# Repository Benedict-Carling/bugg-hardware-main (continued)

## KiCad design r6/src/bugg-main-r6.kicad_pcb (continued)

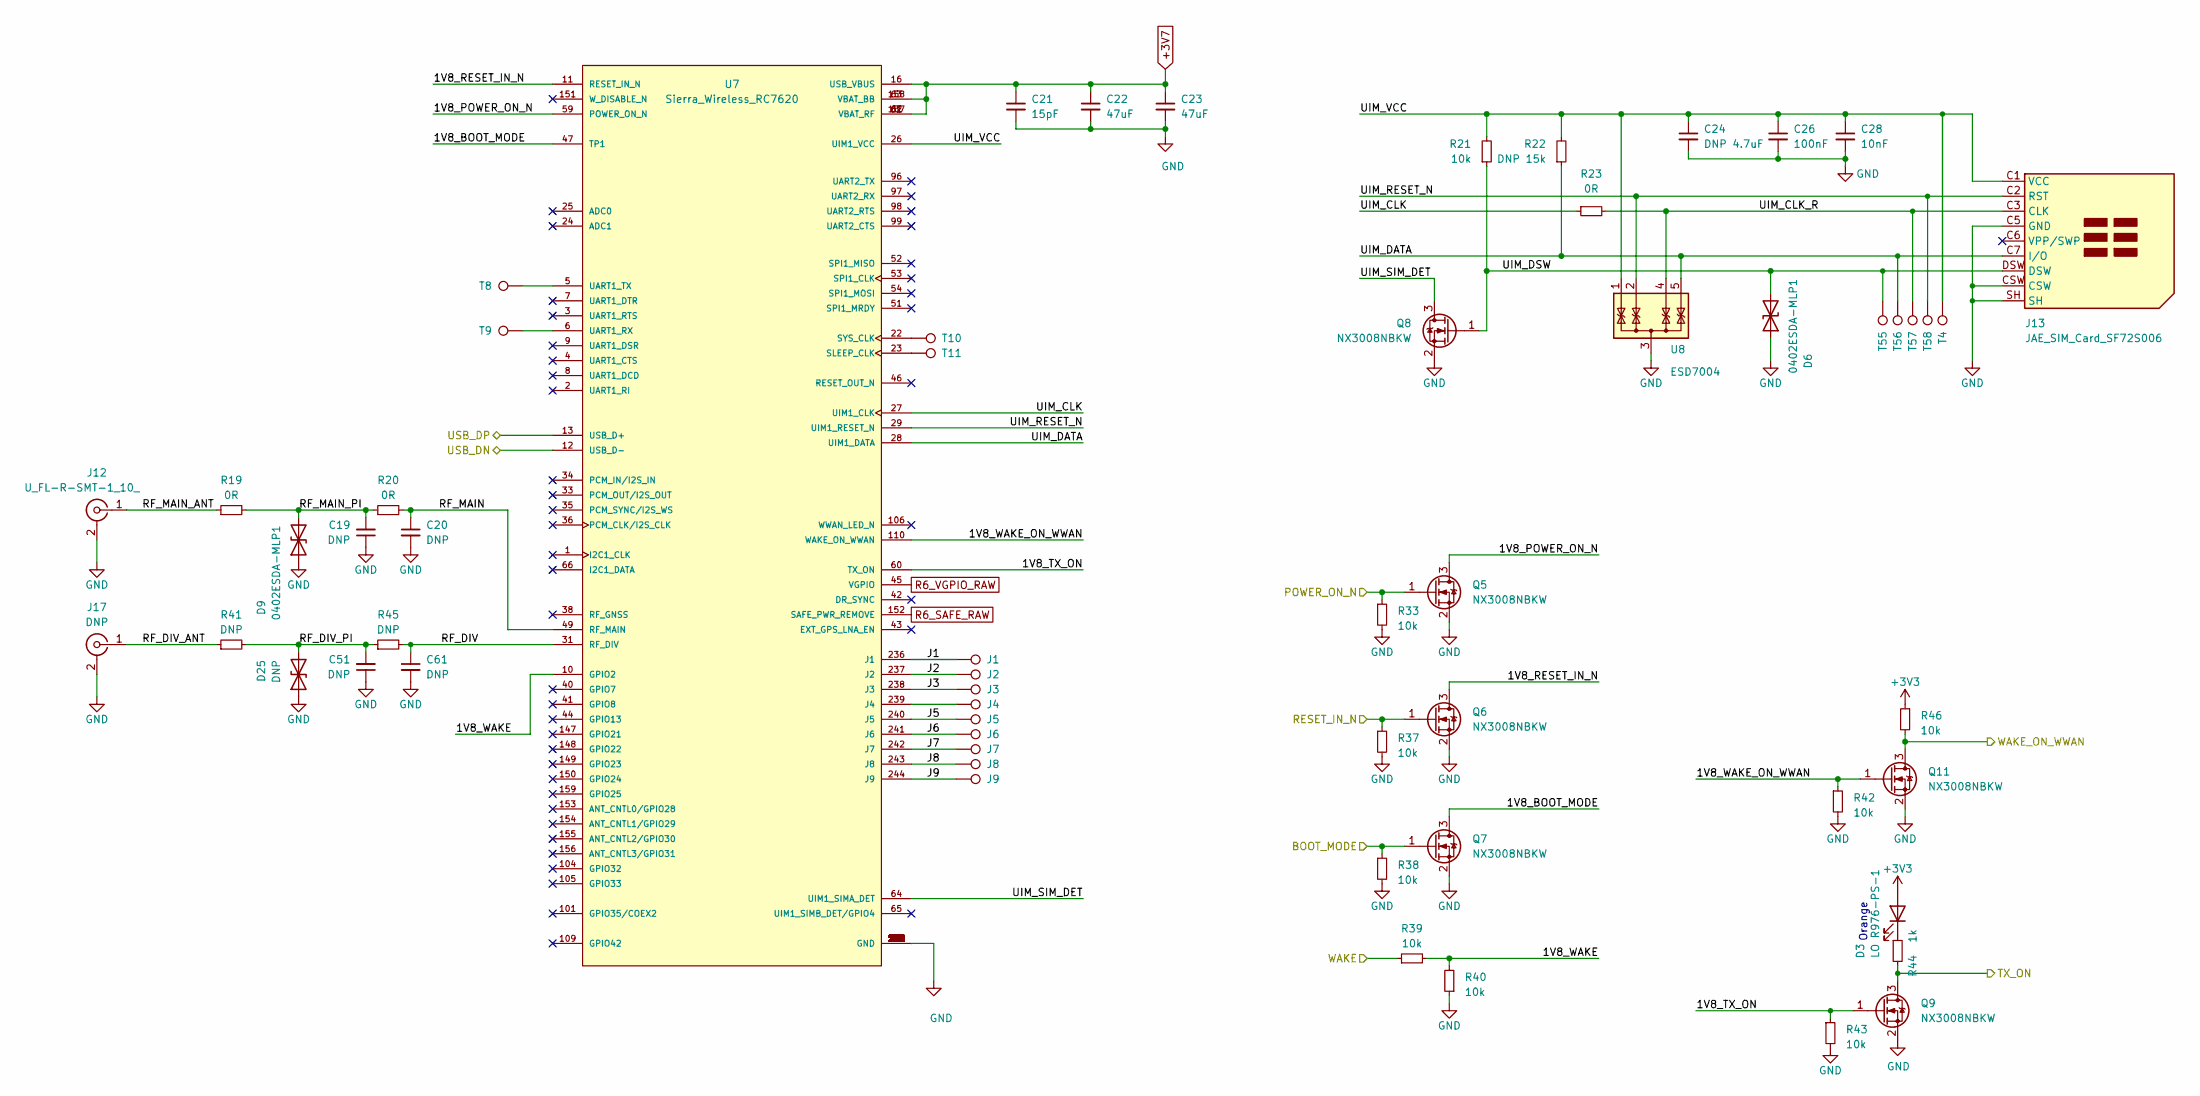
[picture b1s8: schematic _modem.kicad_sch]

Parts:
C19, C20, C51, C61: DNP; C_0402_1005Metric
C21: 15pF; C_0402_1005Metric
C22, C23: 47uF; C_1206_3216Metric; Voltage 6.3V; MPN GRM31CE70J476ME15L; Mouser 81-GRM31CE70J476ME5L
C24: DNP 4.7uF; C_0603_1608Metric
C26: 100nF; C_0402_1005Metric; Voltage 50V; MPN GRM155R71H104KE14D; Mouser 81-GRM155R71H104KE4D
C28: 10nF; C_0402_1005Metric; Voltage 50V
D3: LO R976-PS-1; CHIPLED-0805; MPN LOR976-PS-1; Digikey 475-2488-6-ND
D6, D9: 0402ESDA-MLP1; D_0402_1005Metric; MPN 0402ESDA-MLP1; Digikey 283-2964-6-ND
D25: DNP; D_0402_1005Metric
J1, J2, J3, J4, J5, J6, J7, J8, J9: TestPoint_Pad_D1.0mm
J12: U_FL-R-SMT-1_10_; U.FL_Hirose_U.FL-R-SMT-1-copper-keepout; MPN 128-0711-201; Digikey J983DKR-ND
J13: JAE_SIM_Card_SF72S006; MPN SF72S006VBDR2500; Digikey 670-2967-6-ND
J17: DNP; U.FL_Hirose_U.FL-R-SMT-1-copper-keepout
Q5, Q6, Q7, Q8, Q9, Q11: NX3008NBKW; SOT-323_SC-70; MPN NX3008NBKW; Digikey 1727-1280-6-ND
R19, R20, R23: 0R; R_0402_1005Metric
R21, R33, R37, R38, R39, R40, R42, R43, R46: 10k; R_0402_1005Metric
R22: DNP 15k; R_0402_1005Metric
R41, R45: DNP; R_0402_1005Metric
R44: 1k; R_0402_1005Metric
T4, T8, T9, T10, T11, T55, T56, T57, T58: TestPoint_Pad_D1.0mm
U7: Sierra_Wireless_RC7620; Cellular_Modem-Sierra-Wireless-module-CF3-ringCD; MPN RC7620
U8: ESD7004; USON-10_2.5x1.0mm_P0.5mm; MPN ESD7004MUTAG; Digikey ESD7004MUTAGOSDKR-ND

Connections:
+3V3: D3.2 (A), R46.1; also elsewhere on the board
+3V7: C21.1, C22.1, C23.1, U7.16 (USB_VBUS), U7.61 (VBAT_RF), U7.62 (VBAT_RF), U7.63 (VBAT_BB), U7.157 (VBAT_RF), U7.158 (VBAT_BB); also elsewhere on the board
/BOOT_MODE: Q7.1 (G), R38.1; also elsewhere on the board
/MODEM_USB_DN: U7.12 (USB_D-); also elsewhere on the board
/MODEM_USB_DP: U7.13 (USB_D+); also elsewhere on the board
/Modem/1V8_BOOT_MODE: Q7.3 (D), U7.47 (TP1)
/Modem/1V8_POWER_ON_N: Q5.3 (D), U7.59 (POWER_ON_N)
/Modem/1V8_RESET_IN_N: Q6.3 (D), U7.11 (RESET_IN_N)
/Modem/1V8_TX_ON: Q9.1 (G), R43.1, U7.60 (TX_ON)
/Modem/1V8_WAKE: R39.2, R40.2, U7.10 (GPIO2)
/Modem/1V8_WAKE_ON_WWAN: Q11.1 (G), R42.1, U7.110 (WAKE_ON_WWAN)
/Modem/J1: J1.1, U7.236 (J1)
/Modem/J2: J2.1, U7.237 (J2)
/Modem/J3: J3.1, U7.238 (J3)
/Modem/J5: J5.1, U7.240 (J5)
/Modem/J6: J6.1, U7.241 (J6)
/Modem/J7: J7.1, U7.242 (J7)
/Modem/J8: J8.1, U7.243 (J8)
/Modem/J9: J9.1, U7.244 (J9)
/Modem/RF_DIV: C61.1, R45.2, U7.31 (RF_DIV)
/Modem/RF_DIV_ANT: J17.1 (In), R41.1
/Modem/RF_DIV_PI: C51.2, D25.2 (A2), R41.2, R45.1
/Modem/RF_MAIN: C20.1, R20.2, U7.49 (RF_MAIN)
/Modem/RF_MAIN_ANT: J12.1 (In), R19.1
/Modem/RF_MAIN_PI: C19.2, D9.2 (A2), R19.2, R20.1
/Modem/UIM_CLK: R23.1, U7.27 (UIM1_CLK)
/Modem/UIM_CLK_R: J13.C3 (CLK), R23.2, T57.1, U8.4 (IO3), U8.7
/Modem/UIM_DATA: J13.C7 (I/O), R22.1, T56.1, U7.28 (UIM1_DATA), U8.5 (IO4), U8.6
/Modem/UIM_DSW: D6.2 (A2), J13.DSW, Q8.1 (G), R21.1, T55.1
/Modem/UIM_RESET_N: J13.C2 (RST), T58.1, U7.29 (UIM1_RESET_N), U8.2 (IO2), U8.9
/Modem/UIM_SIM_DET: Q8.3 (D), U7.64 (UIM1_SIMA_DET)
/Modem/UIM_VCC: C24.1, C26.1, C28.1, J13.C1 (VCC), R21.2, R22.2, T4.1, U7.26 (UIM1_VCC), U8.1 (IO1), U8.10
/POWER_ON_N: Q5.1 (G), R33.1; also elsewhere on the board
/RESET_IN_N: Q6.1 (G), R37.1; also elsewhere on the board
/TX_ON: Q9.3 (D), R44.2; also elsewhere on the board
/WAKE: R39.1; also elsewhere on the board
/WAKE_ON_WWAN: Q11.3 (D), R46.2; also elsewhere on the board
GND: C19.1, C20.2, C21.2, C22.2, C23.2, C24.2, C26.2, C28.2, C51.1, C61.2, D6.1 (A1), D9.1 (A1), D25.1 (A1), J12.2 (Ext), J13.C5 (GND), J13.CSW, J13.SH, J17.2 (Ext), Q5.2 (S), Q6.2 (S), Q7.2 (S), Q8.2 (S), Q9.2 (S), Q11.2 (S), R33.2, R37.2, R38.2, R40.1, R42.2, R43.2, U7.30 (GND), U7.32 (GND), U7.37 (GND), U7.39 (GND), U7.48 (GND), U7.50 (GND), U7.67 (GND), U7.68 (GND), U7.69 (GND), U7.70 (GND), U7.111 (GND), U7.113 (GND), U7.125 (GND), U7.128 (GND), U7.136 (GND), U7.139 (GND), U7.167 (GND), U7.168 (GND), U7.169 (GND), U7.170 (GND), U7.171 (GND), U7.172 (GND), U7.173 (GND), U7.174 (GND), U7.175 (GND), U7.176 (GND), U7.177 (GND), U7.178 (GND), U7.179 (GND), U7.180 (GND), U7.181 (GND), U7.182 (GND), U7.183 (GND), U7.184 (GND), U7.185 (GND), U7.186 (GND), U7.187 (GND), U7.188 (GND), U7.189 (GND), U7.190 (GND), U7.191 (GND), U7.192 (GND), U7.193 (GND), U7.194 (GND), U7.195 (GND), U7.196 (GND), U7.197 (GND), U7.198 (GND), U7.199 (GND), U7.200 (GND), U7.201 (GND), U7.202 (GND), U7.203 (GND), U7.204 (GND), U7.205 (GND), U7.206 (GND), U7.207 (GND), U7.208 (GND), U7.209 (GND), U7.210 (GND), U7.211 (GND), U7.212 (GND), U7.213 (GND), U7.214 (GND), U7.215 (GND), U7.216 (GND), U7.217 (GND), U7.218 (GND), U7.219 (GND), U7.220 (GND), U7.221 (GND), U7.222 (GND), U7.223 (GND), U7.224 (GND), U7.225 (GND), U7.226 (GND), U7.227 (GND), U7.228 (GND), U7.229 (GND), U7.230 (GND), U7.231 (GND), U7.232 (GND), U7.233 (GND), U7.234 (GND), U8.3 (G), U8.8; also elsewhere on the board
unnamed: D3.1 (K), R44.1
unnamed: J4.1, U7.239 (J4)
unnamed: T11.1, U7.23 (SLEEP_CLK)
unnamed: T10.1, U7.22 (SYS_CLK)
unnamed: T9.1, U7.6 (UART1_RX)
unnamed: T8.1, U7.5 (UART1_TX)
R6_SAFE_RAW: U7.152 (SAFE_PWR_REMOVE); also elsewhere on the board
R6_VGPIO_RAW: U7.45 (VGPIO); also elsewhere on the board

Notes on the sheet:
Orange

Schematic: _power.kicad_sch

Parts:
C1, C3, C4, C41, C42, C93: 220nF; C_0402_1005Metric; Voltage 50V; MPN GRM155R61H224ME01J; Digikey 490-GRM155R61H224ME01JDKR-ND
C2, C5, C6, C43, C44, C45, C80, C88, C89, C90, C91, C133, C134, C135, C136: 4.7uF; C_1206_3216Metric; Voltage 50V; MPN CL31B475KBHNNNE
C7, C8, C97, C98, C99, C100, C111, C120: 1uF; C_0402_1005Metric; Voltage 6.3V; MPN GRM155C81C105KE15D; Mouser 81-GRM155C81C105KE5D
C9, C10, C17, C18, C87, C101, C105, C106, C117, C121, C138, C139, C141: 100nF; C_0402_1005Metric; Voltage 50V; MPN GRM155R71H104KE14D; Mouser 81-GRM155R71H104KE4D
C11: 18pF; C_0402_1005Metric
C12: 15pF; C_0402_1005Metric
C13, C14, C15, C16, C103: 47uF; C_1206_3216Metric; Voltage 6.3V; MPN GRM31CE70J476ME15L; Mouser 81-GRM31CE70J476ME5L
C85, C86, C140: 4.7uF; C_0603_1608Metric; Voltage 6.3V; MPN CL10A475KQ8NNNC
C92, C116: 3.3pF; C_0402_1005Metric
C94, C122, C123, C124, C125, C126: DNP; C_0402_1005Metric
C95: 4.7nF; C_0402_1005Metric
C96, C113, C115: 10nF; C_0402_1005Metric; Voltage 50V
C102, C104: 10uF; C_0603_1608Metric; Voltage 6.3V; MPN CL10A106MQ8NNNC; Mouser 187-CL10A106MQ8NNNC
C107, C108, C109: 10uF; C_1210_3225Metric; Voltage 50V; MPN GCM32EC71H106KA03L; Mouser 81-GCM32EC71H106KA3L
C110, C114: 5.8pF; C_0402_1005Metric
C112: 180pF; C_0402_1005Metric
C118, C119: 22uF; CP_Elec_5x5.8; Voltage 25V; MPN UCL1E220MCL1GS; Digikey 493-3932-1-ND
C127, C128, C129, C130, C131: DNP; C_1206_3216Metric
D4: ATV02W360B-HF; D_SOD-123; MPN ATV02W360B-HF; Digikey 641-1664-6-ND
D5: 12V; D_SOD-123; MPN BZT52C12-13-F; Digikey BZT52C1213-FDIDKR-ND
D16, D17, D18, D19: PMEG6020ETR; Nexperia_CFP3_SOD-123W; MPN PMEG6020ETR,115; Digikey 1727-1347-1-ND
D21, D22: SMF4L48CA; D_SOD-123F; MPN SMF4L48CA; Mouser 576-SMF4L48CA
D23, D24: DNP; D_SOD-123F
FB3, FB4, FB5, FB6: 1k@100MHz; L_0603_1608Metric; MPN BLM18KG102SN1D; Digikey 490-17349-1-ND
J10: 502443-0860; Molex_CLIK-Mate_502443-0870_1x08-2MP_P2.00mm_Vertical; MPN 502443-0860; Digikey Molex
L1: 4.7uH; L_Coilcraft_XAL5030-XXX; MPN XAL5030-472MEC; Mouser 994-XAL5030-472MEC
L2: 3.3uH; L_Coilcraft_XAL5030-XXX; MPN XAL5030-332MEC; Mouser 994-XAL5030-332MEC
L3, L4: 4.7uH; L_Coilcraft_XxL4030; MPN XAL4030-472MEC; Mouser 994-XAL4030-472MEC
L5: 15uH; L_Wuerth_MAPI-4020; MPN 74438356150; Mouser 710-74438356150
L6, L7, L8: 1uH; L_1008_2520Metric; MPN LQM2HPN1R0MJHL; Digikey 490-12068-6-ND
NT1: NetTie_2; NetTie-2_SMD_Pad2.0mm-inner1
Q1, Q2, Q3: Si7113ADN; Vishay_PowerPAK_1212-8_Single; MPN SI7113ADN-T1-GE3; Digikey SI7113ADN-T1-GE3DKR-ND
Q10: Si2323DS; SOT-23; MPN SI2323DS-T1
Q26: 2SD1782KT146R; SC-59; MPN 2SD1782KT146R; Mouser 755-2SD1782KT146R
R6: 10k; R_0402_1005Metric
R7, R8, R11, R12, R13, R14, R16, R88: 100k; R_0402_1005Metric
R9, R10, R90: 1M; R_0402_1005Metric
R15: 22.6k; R_0402_1005Metric
R17: 37.4k; R_0402_1005Metric
R18, R83, R99, R102, R103, R107, R108: 0R; R_0402_1005Metric
R35, R36: 0.1R; R_0402_1005Metric
R78, R101: DNP; R_0402_1005Metric
R87: 100R; R_0402_1005Metric
R89, R98: 510R; R_0402_1005Metric
R91: 976k; R_0402_1005Metric
R92: 85.6k; R_0402_1005Metric
R93: 105k; R_0402_1005Metric
R94: 1.3M; R_0402_1005Metric
R95: 34.8k; R_0402_1005Metric
R96: 180k; R_0402_1005Metric
R97: 45.3k; R_0402_1005Metric
R104: 100R; R_0603_1608Metric; MPN RC0603FR-07100RL
R105, R109, R110: 0R; R_0603_1608Metric
R111, R112: DNP; R_0805_2012Metric
T1, T2, T5, T6, T7, T12, T13, T17, T21, T22, T36, T41, T42, T51, T52: TestPoint_Pad_D1.0mm
U2: ESD7004; USON-10_2.5x1.0mm_P0.5mm; MPN ESD7004MUTAG; Digikey ESD7004MUTAGOSDKR-ND
U3, U4: DZDH0401DW; SOT-363_SC-70-6; MPN DZDH0401DW; Digikey 31-DZDH0401DW-7DKR-ND
U5, U6: LM60440DRPK; WQFN-HR-13; MPN LM60440DRPK; Digikey 595-LM60440DRPKR
U28: TPS65130RGE; VQFN-24-1EP_4x4mm_P0.5mm_EP2.45x2.45mm_ThermalVias; MPN TPS65130RGE; Digikey 296-41861
U29: NCP163ASN330T1G; SOT-23-5; MPN NCP163ASN330T1G; Mouser 863-NCP163ASN330T1G
U30: NCP163ASN180T1G; SOT-23-5; MPN NCP163ASN180T1G; Mouser 863-NCP163ASN180T1G
U31: MAX6105; SOT-23; MPN MAX6105EUR+T; Digikey MAX6105EUR+TCT-ND
U32: LT8362xDD; DFN-10-1EP_3x3mm_P0.5mm_EP1.65x2.38mm; MPN LT8362; Mouser LT8362HDD#PBF
U33: LM7121IM; SOIC-8_3.9x4.9mm_P1.27mm; MPN LM7121IM; Mouser 926-LM7121IMX/NOPB
U35: TPS22810DBV; SOT-23-6; MPN TPS22810DBV; Mouser 595-TPS22810TDBVRQ1

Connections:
+1V8: R105.1; also elsewhere on the board
+3.3VA: R104.1; also elsewhere on the board
+3.3VADC: T2.1, U35.5 (QOD), U35.6 (VOUT); also elsewhere on the board
+3V3: C120.2, U35.1 (VIN); also elsewhere on the board
+3V7: R109.1; also elsewhere on the board
+5V: C86.1, C97.1, C99.1, C101.1, C102.1, C140.1, C141.1, FB3.1, FB4.1, L6.1, Q10.2 (S), R78.1, R87.1, R110.1, U28.5 (INN), U28.6 (INN), U31.1 (IN); also elsewhere on the board
+5VA: T51.1, U31.2 (OUT), U33.3 (+); also elsewhere on the board
+15V: C117.1, R102.1, U33.7 (V+); also elsewhere on the board
+48V: R108.1; also elsewhere on the board
-15V: C121.2, R103.2, U33.4 (V-); also elsewhere on the board
/3V7_EN: R6.1, U6.9 (EN); also elsewhere on the board
/48V_EN: U32.1 (EN/UVLO); also elsewhere on the board
/EXT_MIC_EN: R18.1, R83.1, R88.2, T1.1, U29.3 (EN), U30.3 (EN), U35.3 (EN/UVLO); also elsewhere on the board
/MIC_IN_N: D21.2 (A2), D23.2 (A2), J10.6; also elsewhere on the board
/MIC_IN_P: D22.2 (A2), D24.2 (A2), J10.7; also elsewhere on the board
/P3V3_OUT: R99.2; also elsewhere on the board
/Power and input connector/1V8_O: C100.1, R105.2, T42.1, U30.5 (VOUT)
/Power and input connector/3V7_O: C12.1, C14.1, C16.1, C18.1, L2.2, R13.1, R16.1, R109.2, T12.1
/Power and input connector/5V_O: C11.1, C13.1, C15.1, C17.1, L1.2, Q1.1 (S), Q1.2 (S), Q1.3 (S), R12.1, R14.1, R110.2, T13.1, U3.4 (SOURCE)
/Power and input connector/48V_O: C80.1, C115.1, D19.2 (A), Q26.2 (E), R108.2, T5.1
/Power and input connector/+5V_SW: C85.1, L3.1, Q10.3 (D), R78.2
/Power and input connector/+15V_L: C118.1, FB5.1, R102.2, R111.2, T21.1
/Power and input connector/-15V_L: C119.2, FB6.2, R103.1, R112.1, T22.1
/Power and input connector/BSW: Q10.1 (G), U28.7 (BSW)
/Power and input connector/CN: C95.1, U28.18 (CN)
/Power and input connector/CP: C96.1, U28.21 (CP)
/Power and input connector/FBN: R93.2, R94.1, R101.1, U28.16 (FBN)
/Power and input connector/FBP: C92.2, R91.2, R92.1, U28.22 (FBP)
/Power and input connector/FBX: C110.2, R90.2, R95.1, U32.6 (FBX)
/Power and input connector/INP: D16.2 (A), L3.2, U28.1 (INP), U28.24 (INP)
/Power and input connector/INTVCC: C111.1, U32.3 (INTVCC)
/Power and input connector/LT_VIN: C103.1, C104.2, L5.1, L6.2, T7.1, U32.2 (VIN)
/Power and input connector/LT_VOUT: C105.1, C106.1, C107.1, C108.1, C110.1, D18.1 (K), Q26.3 (C), R89.1, R90.1, T6.1
/Power and input connector/OUTN: D17.1 (K), L4.2, U28.13 (OUTN), U28.14 (OUTN)
/Power and input connector/RT: R97.1, U32.7 (RT)
/Power and input connector/SS: C113.1, U32.8 (SS)
/Power and input connector/SW_3V7: L2.1, U6.12 (SW)
/Power and input connector/SW_5V4: L1.1, U5.12 (SW)
/Power and input connector/SW_48: D18.2 (A), L5.2, U32.10 (SW)
/Power and input connector/TPS_VREF: C93.1, R93.1, U28.17 (VREF)
/Power and input connector/VC: C114.1, R96.1, U32.5 (VC)
/Power and input connector/VIN_DCDC_3V7: C3.1, C5.1, C41.1, L8.2, R36.1, U6.2 (VIN), U6.10 (VIN)
/Power and input connector/VIN_DCDC_5: C4.1, C6.1, C42.1, L7.2, R35.1, U5.2 (VIN), U5.9 (EN), U5.10 (VIN)
/Power and input connector/VIN_F: C87.1, R87.2, U28.4 (VIN)
/Power and input connector/VIN_LDO_1V8: FB4.2, U30.1 (VIN)
/Power and input connector/VIN_LDO_3V3: FB3.2, U29.1 (VIN)
/Power and input connector/VNEG: C90.2, C91.2, C94.2, C134.2, C136.2, C139.2, D17.2 (A), FB6.1, R94.2, U28.15 (VNEG)
/Power and input connector/VPOS: C88.1, C89.1, C92.1, C133.1, C135.1, C138.1, D16.1 (K), FB5.2, R91.1, U28.23 (VPOS)
/Power and input connector/VREF_O: C116.1, R98.2, R107.1, T52.1, U33.6
/Power and input connector/Vin: C1.1, C2.1, C43.1, D5.1 (K), L7.1, L8.1, Q2.1 (S), Q2.2 (S), Q2.3 (S), Q3.1 (S), Q3.2 (S), Q3.3 (S), U4.4 (SOURCE)
/USB_UART_DN: J10.1, U2.1 (IO1), U2.10; also elsewhere on the board
/USB_UART_DP: J10.2, U2.2 (IO2), U2.9; also elsewhere on the board
/VREF: R107.2; also elsewhere on the board
GND: C1.2, C2.2, C3.2, C4.2, C5.2, C6.2, C7.1, C8.1, C13.2, C14.2, C15.2, C16.2, C17.2, C18.2, C41.2, C42.2, C43.2, C44.2, C45.2, C120.1, C122.2, C123.2, C124.2, C125.2, C126.2, C127.2, C128.2, C129.2, C130.2, C131.2, D4.1 (A1), D21.1 (A1), D22.1 (A1), J10.5, NT1.1, R6.2, R7.2, R8.2, R9.2, R10.2, R11.2, R15.2, R17.2, T17.1, T36.1, U2.3 (G), U2.8, U5.1 (PGND), U5.6 (AGND), U5.11 (PGND), U5.13 (PGND), U6.1 (PGND), U6.6 (AGND), U6.11 (PGND), U6.13 (PGND), U35.2 (GND); also elsewhere on the board
GNDA: C80.2, C85.2, C86.2, C87.2, C88.2, C89.2, C90.1, C91.1, C93.2, C95.2, C96.2, C97.2, C98.2, C99.2, C100.2, C101.2, C102.2, C103.2, C104.1, C105.2, C106.2, C107.2, C108.2, C109.2, C111.2, C112.2, C113.2, C114.2, C115.2, C117.2, C118.2, C119.1, C121.1, C122.1, C123.1, C124.1, C125.1, C126.1, C127.1, C128.1, C129.1, C130.1, C131.1, C133.2, C134.1, C135.2, C136.1, C138.2, C139.1, C140.2, C141.2, D23.1 (A1), D24.1 (A1), J10.8, L4.1, NT1.2, R88.1, R92.2, R95.2, R97.2, R111.1, R112.2, U28.2 (PGND), U28.3 (PGND), U28.9 (PSP), U28.11 (PSN), U28.19 (AGND), U28.25 (EP), U29.2 (GND), U30.2 (GND), U31.3 (GND), U32.4 (BIAS), U32.9 (SYNC/MODE), U32.11 (GND); also elsewhere on the board
IN_VIN: D4.2 (A2), J10.3, Q3.5 (D); also elsewhere on the board
unnamed: C44.1, R35.2
unnamed: C45.1, R36.2
unnamed: C94.1, R101.2
unnamed: C112.1, R96.2
unnamed: D5.2 (A), Q3.4 (G), R11.1
unnamed: C109.1, D19.1 (K), Q26.1 (B), R89.2
unnamed: Q1.4 (G), R9.1, U3.3 (BIAS)
unnamed: Q2.4 (G), R10.1, U4.3 (BIAS)
unnamed: R7.1, U3.2 (REF)
unnamed: R8.1, U4.2 (REF)
unnamed: C9.2, U5.4 (BOOT)
unnamed: C11.2, R14.2, R15.1, U5.7 (FB)
unnamed: R12.2, U5.8 (PG)
unnamed: C9.1, U5.3 (SW_BT)
unnamed: C7.2, U5.5 (VCC)
unnamed: C10.1, U6.4 (BOOT)
unnamed: C12.2, R16.2, R17.1, U6.7 (FB)
unnamed: R13.2, U6.8 (PG)
unnamed: C10.2, U6.3 (SW_BT)
unnamed: C8.2, U6.5 (VCC)
unnamed: R83.2, U28.10 (ENN)
unnamed: R18.2, U28.8 (ENP)
unnamed: C116.2, R98.1, U33.2 (-)
R6_3V3_RAW: C98.1, R104.2, T41.1, U29.5 (VOUT); also elsewhere on the board
VBUS: J10.4, Q1.5 (D), Q2.5 (D), R99.1, U2.4 (IO3), U2.5 (IO4), U2.6, U2.7, U3.6 (DRAIN), U4.6 (DRAIN); also elsewhere on the board

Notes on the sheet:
Special op-amp stable with unlimited Cload for driving C77
Output 5.4V at 4A max Extra 0.4V ensures IN_VIN priority over I_VUSB_5V if both are connected, and exceeds 5.0V reference IC max dropout of 200mV
Input 6-36V
GNDA Domain
Vneg = -1.213 * (R94/R93) = -15.02V
VDD is actually 5.4V. Satisfies max dropout of 200mV
P48 microphone phantom. Capacitance multiplier for ultra-low ripple. Simulated <100uVpp
Output 3.7V at 4A max
Switch digital supply into the external mic interface U35 discharges +3.3VADC to GND when turned off.
ADC core voltage
Preamp and ADC driver rails
GND Domain
PIP and 3.3V microphone power
Vpos = 1.213 * (R91/R92 + 1) = 15.04V
ADC reference

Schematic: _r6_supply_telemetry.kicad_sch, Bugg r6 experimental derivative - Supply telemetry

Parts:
C144: 100nF; C_0402_1005Metric; MPN CL05B104KO5NNNC
C145, C146, C147, C148: 10nF; C_0402_1005Metric; MPN CL05B103KB5NNNC
R213: 150k; R_0402_1005Metric; MPN RT0402BRD07150KL
R214, R216, R217, R218, R220: 10k; R_0402_1005Metric; MPN RT0402BRD0710KL
R215, R219: 20k; R_0402_1005Metric; MPN RT0402BRD0720KL
U38: ADS1115IDGSR; MSOP-10_3x3mm_P0.5mm; MPN ADS1115IDGSR

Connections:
+3V7: R217.1; also elsewhere on the board
+5V: R215.1; also elsewhere on the board
GND: C144.2, C145.2, C146.2, C147.2, C148.2, R214.2, R216.2, R218.2, R220.2, U38.1 (ADDR), U38.3 (GND); also elsewhere on the board
IN_VIN: R213.1; also elsewhere on the board
R6_3V7_SENSE: C147.1, R217.2, R218.1, U38.6 (AIN2)
R6_5V_SENSE: C146.1, R215.2, R216.1, U38.5 (AIN1)
R6_AON3V3: C144.1, U38.8 (VDD); also elsewhere on the board
R6_SCL: U38.10 (SCL); also elsewhere on the board
R6_SDA: U38.9 (SDA); also elsewhere on the board
R6_USB_SENSE: C148.1, R219.2, R220.1, U38.7 (AIN3)
R6_VIN_SENSE: C145.1, R213.2, R214.1, U38.4 (AIN0)
VBUS: R219.1; also elsewhere on the board

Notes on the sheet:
Divider ratios: VIN 16:1, 5V 3:1, modem 2:1, USB 3:1. ADC +/-4.096 V gives 125 uV/code at ADC. Not a current monitor.

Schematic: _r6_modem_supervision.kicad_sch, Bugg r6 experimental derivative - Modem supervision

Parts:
C149, C150, C151: 100nF; C_0402_1005Metric; MPN CL05B104KO5NNNC
Q31, Q32: BC847B,215; SOT-23; MPN BC847B,215
R221, R224: 47k; R_0402_1005Metric; MPN RC0402FR-0747KL
R222, R225: 470k; R_0402_1005Metric; MPN RC0402FR-07470KL
R223, R226, R227: 10k; R_0402_1005Metric; MPN RC0402FR-0710KL
R228: 100k; R_0402_1005Metric; MPN RC0402FR-07100KL
U39: TCA9536DGKR; VSSOP-8_3x3mm_P0.65mm; MPN TCA9536DGKR
U40: SN74LVC1G74DCUR; VSSOP-8_2.3x2mm_P0.5mm; MPN SN74LVC1G74DCUR
U41: SN74LVC2G17DCKR; SOT-363_SC-70-6; MPN SN74LVC2G17DCKR

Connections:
+3V3: C149.1, C150.1, C151.1, R223.2, R226.2, U39.8 (VCC), U40.2 (D), U40.7 (PRE_N), U40.8 (VCC), U41.5 (VCC); also elsewhere on the board
GND: C149.2, C150.2, C151.2, Q31.2 (E), Q32.2 (E), R222.2, R225.2, R227.2, R228.2, U39.4 (GND), U40.4 (GND), U41.2 (GND); also elsewhere on the board
R6_LATCH_ARM: R227.1, U39.3 (P2), U40.6 (CLR_N)
R6_MODEM_BASE0: Q31.1 (B), R221.2, R222.1
R6_MODEM_BASE1: Q32.1 (B), R224.2, R225.1
R6_SAFE_CLK: U40.1 (CLK), U41.4 (2Y)
R6_SAFE_COL: Q32.3 (C), R226.1, U41.3 (2A)
R6_SAFE_LATCH: U39.2 (P1), U40.5 (Q)
R6_SAFE_RAW: R224.1; also elsewhere on the board
R6_SCL: U39.6 (SCL); also elsewhere on the board
R6_SDA: U39.7 (SDA); also elsewhere on the board
R6_SPARE: R228.1, U39.5 (P3_INT)
R6_VGPIO_COL: Q31.3 (C), R223.1, U41.1 (1A)
R6_VGPIO_N: U39.1 (P0), U41.6 (1Y)
R6_VGPIO_RAW: R221.1; also elsewhere on the board

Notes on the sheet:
U40 captures trailing edge of SAFE_PWR_REMOVE. Arm before AT!POWERDOWN; require Q=1 AND VGPIO_N=1 before removing +3V7.

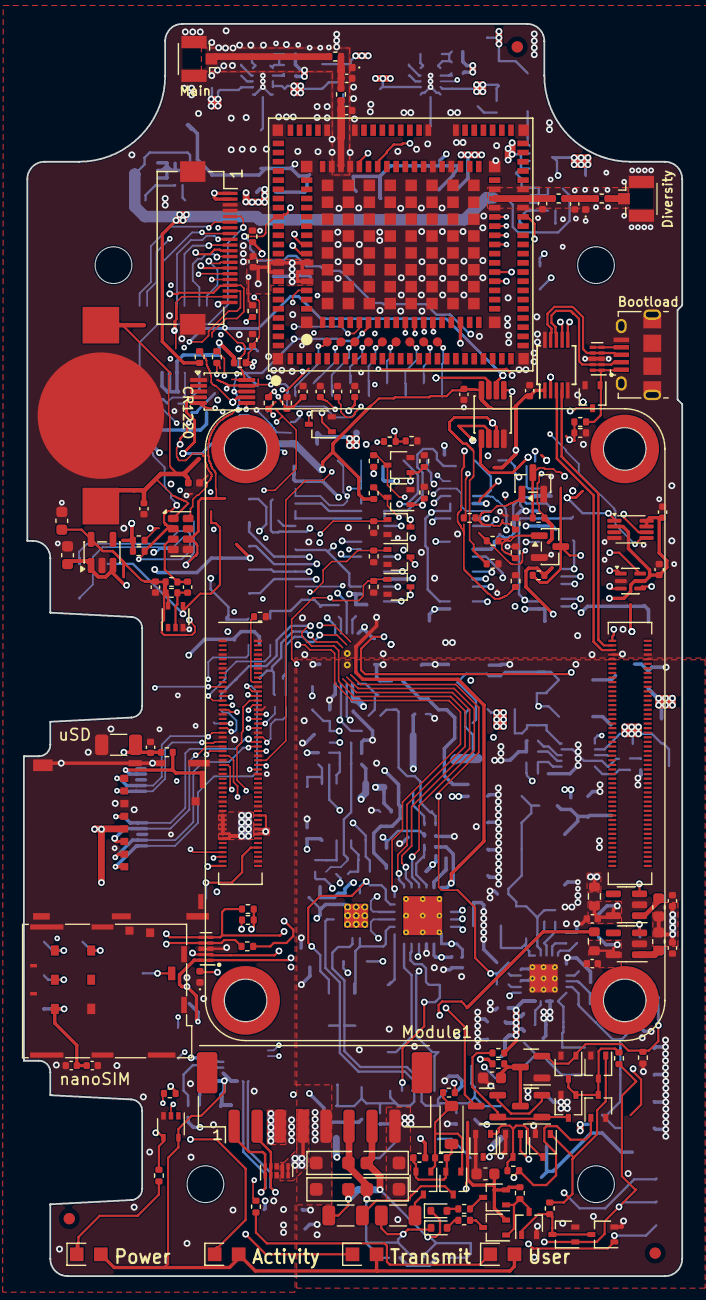
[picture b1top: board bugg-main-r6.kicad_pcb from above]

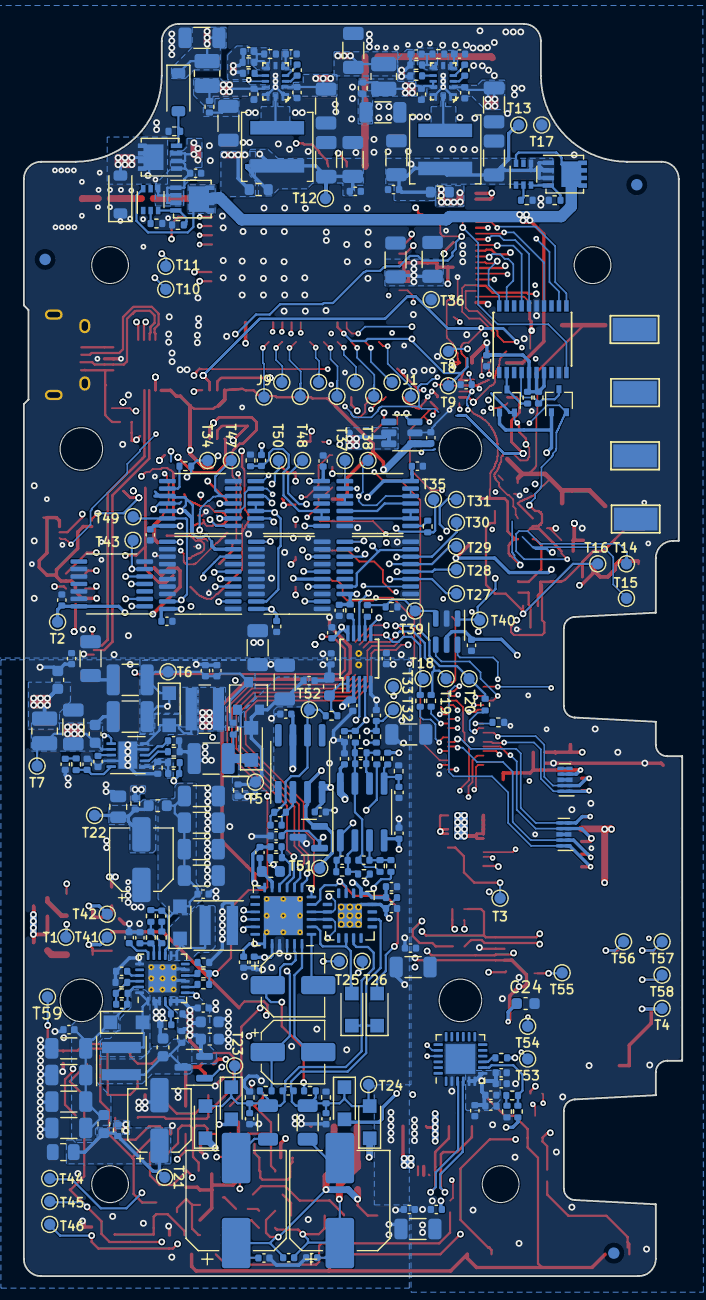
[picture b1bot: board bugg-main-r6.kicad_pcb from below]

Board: 6 copper layers, 57.3 x 109.0 mm, 493 parts (327 on the bottom side), 258 nets.
